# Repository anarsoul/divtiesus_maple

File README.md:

# [DivTIESUS Maple Edition](https://anarsoul.github.io/divtiesus_maple)
DivTIESUS Maple Edition is a SD/MMC card interface for the ZX Spectrum. It is based on Miguel's [DivTIESUS](https://github.com/mcleod-ideafix/divtiesus), but adds joystick port and serial port for WiFi at the expense of Soft +3E feature. I redid whole project in KiCAD and rerouted the PCB. CPLD pin assignment has been changed to accommodate new PCB layout.

You can [buy me a coffee](https://ko-fi.com/anarsoul) if you want to say thank you.

# Features
- DivMMC compatible interface with 8 KiB of EEPROM and 128 KiB or 512 KiB of RAM. Standard utils for EEPROM flashing, as provided by the ESXDOS team, are compatible with DivTIESUS.
- Model autodetection. This means you don't need to put a jumper, or flip a switch to change from using it with a Spectrum 48K and a +3.
- Tested with original Spectrum+, Black +2, Harlequin 128 rev. 2D and rev. 4B, Karabas 128 rev. B1. More testing reports will be appreciated
- It uses its own fast clock (24 MHz). It does not need the CPU clock at all.
- NMI button to call file browser in ESXDOS, and handy RESET button.
- MicroSD card slot
- DIP switches for enabling EEPROM flashing and disabling auto-mapping (bottom switch) and for disabling built-in joystick interface (top switch)
- Optional: Zx-Uno-compatible UART (running at 115200 baud) with WiFi. Do not place ESP12 if you are not planning to use it
- Optional: Built-in Kempston joystick interface, compatible with either Atari-style joystick or Sega Genesis joystick (3 or 6-button). Do not place DB9 connector and U6 (74HC165) if you are not planning to use it and disable it with a DIP switch. All 3 buttons are implemented (so called "extended Kempston")
- Joystick interface maps "A" button as "UP" if "Start" button is pressed during machine reset.
- Visual feedback for SD activity (blue led)
- ESXDOS shadowing does not collide with all-RAM feature in +2A/B/3 machines. If the system is in all-RAM mode, ESXDOS ROM mapping is disabled.
- Included STLs for 3D printing an enclosure

# Pictures

# Schematic

Schematics can be found [here](out/schematics.pdf)

# Build
- First, you need the DivTIESUS Maple Edition PCB. You can order it from JLCPCB or from PCBWay using `divtiesus_maple_rev2.zip` file from out directory. There is also a [project on PCBWay](https://www.pcbway.com/project/shareproject/DivTIESUS_Maple_Edition_rev_2_c9d0d700.html) if you want to support me
- Second, source the components. Most of the components are rather standard so you can buy it off DigiKey or Mouser. All of them can also be obtained from AliExpress. Be careful with components from Aliexpress, especially if the price is too good to be true

## Bill of materials

Interactive BOM can be found [here](out/bom/ibom.html)

Links to some components:

|Qty|Component|Link|
|--------|---------|--------|
|1|EPM240T100|[link](https://www.aliexpress.com/item/1005003990429762.html)|
|1|DIP switches, 2 position|[link](https://www.aliexpress.com/item/33027764033.html)|
|1|RAM|[link](https://www.aliexpress.com/item/1005002495799688.html)|
|1|EEPROM|[link](https://www.aliexpress.com/item/1005003773070206.html)|
|1|ZX Bus connector, 56pin|[link](https://www.aliexpress.com/item/1005002212044956.html)|
|2|Buttons, 6x6x6H|[link](https://www.aliexpress.com/item/1005005129319965.html)|
|1|microSD slot|[link](https://www.aliexpress.com/item/1005006255074403.html)|
|1|Crystal oscillator, 24Mhz|[link](https://www.aliexpress.com/item/1005005879624979.html)|

- The oscillator does not need to be 24 MHz, but if you use a different value, you'll have to resynthesize CPLD image, otherwise WiFi will not work
- I usually start with placing the CPLD first and programming it. Note: you'll need to supply 3.3V in order to program CPLD, there are GND and 3.3V test points left for this purpose. I source CPLDs from Aliexpress and some of them are coming dead. It is easier to test and replace it before the rest of the components are populated.
- Then place the passives (resistors, resistor arrays, capacitors) and the LED
- Then RAM, EEPROM, microSD socket, DB9 connector and ESP12. You can either leave EEPROM blank or preprogram it. Either way is fine, it can be programmed in-system later, but having EEPROM with known contents may simplify troubleshooting

## First electrical testing
- Check that there is no shorts on the 5V and 3.3V power rails.
- Use a microscope or a magnifying glass to check that there is no shorts between adjacent pads at the CPLD chip.

After all the checks, proceed to build and solder the ZX Spectrum bus connector:

## ZX Spectrum bus connector
- Take the 2x28 pin edge connector and cut about 1-2mm on each side to leave the ends opened, refer to original DivTIESUS README.
- Pull and extract the two metal contacts that are positioned at 5th place, where the index tab will be placed
- Now take a small piece you can get from a PCB, 1.5mm thick and 7mm tall. This will be the index tab.
- As an alternative, you can 3D-print the tab, you can find the model [here](https://www.thingiverse.com/thing:6556638)
- Place the tab in the index hole. Sand it if it's too tall for the hole.
- Using a pair of pliers, push it in place. If it's too small for the hole, use some glue to keep it from coming loose.

Now the edge connector is ready to work as a ZX Spectrum rear bus connector!

## Enclosure

Enclosure can be printed in pretty much any plastic. You need `button-2-nmi.stl`, `button-2-reset.stl`, `enclosure.stl` and `enclosure_top.stl` or `enclosure_top_no_jtag_no_switch.stl` if you don't want the holes for JTAG and the switch. Personally, I printed the parts in PLA and PETG. ABS should work as well. Keep in mind that PLA will soften at ~60C, so avoid using it for enclosure if you are planning to use the device with an original machine. Modern clones are fine, they are usually using CMOS ICs and modern voltage regulators that do not produce much heat.

First, place the buttons, short button (reset) closer to the edge

Then insert the PCB. Be careful to keep it straight and don't let the buttons to fall out

Use 4 M2x8 screws to fix enclosure top

## WiFi

DivTiesus Maple Edition implements Zx-Uno-compatible UART, so software compiled for Zx-Uno should work with it.

I recommend using Nihirash's software, [Netman](https://github.com/nihirash/netman-zx) and [Moon Rabbit](https://github.com/nihirash/moon-rabbit-zx). The binaries can be found [here](tools/wifi/zxwifi.zip) - just unpack them onto your SD card and run `netman/NETMAN.BAS` to configure WiFi. WiFi configuration is persistent, so it needs to be done once. Once WiFi is configured you can run `moon_rabbit/MOONR.BAS` to browse gopher sites.

You can also check out my tool for transferring files from PC to Spectrum: [zxmit](https://github.com/anarsoul/zxmit)

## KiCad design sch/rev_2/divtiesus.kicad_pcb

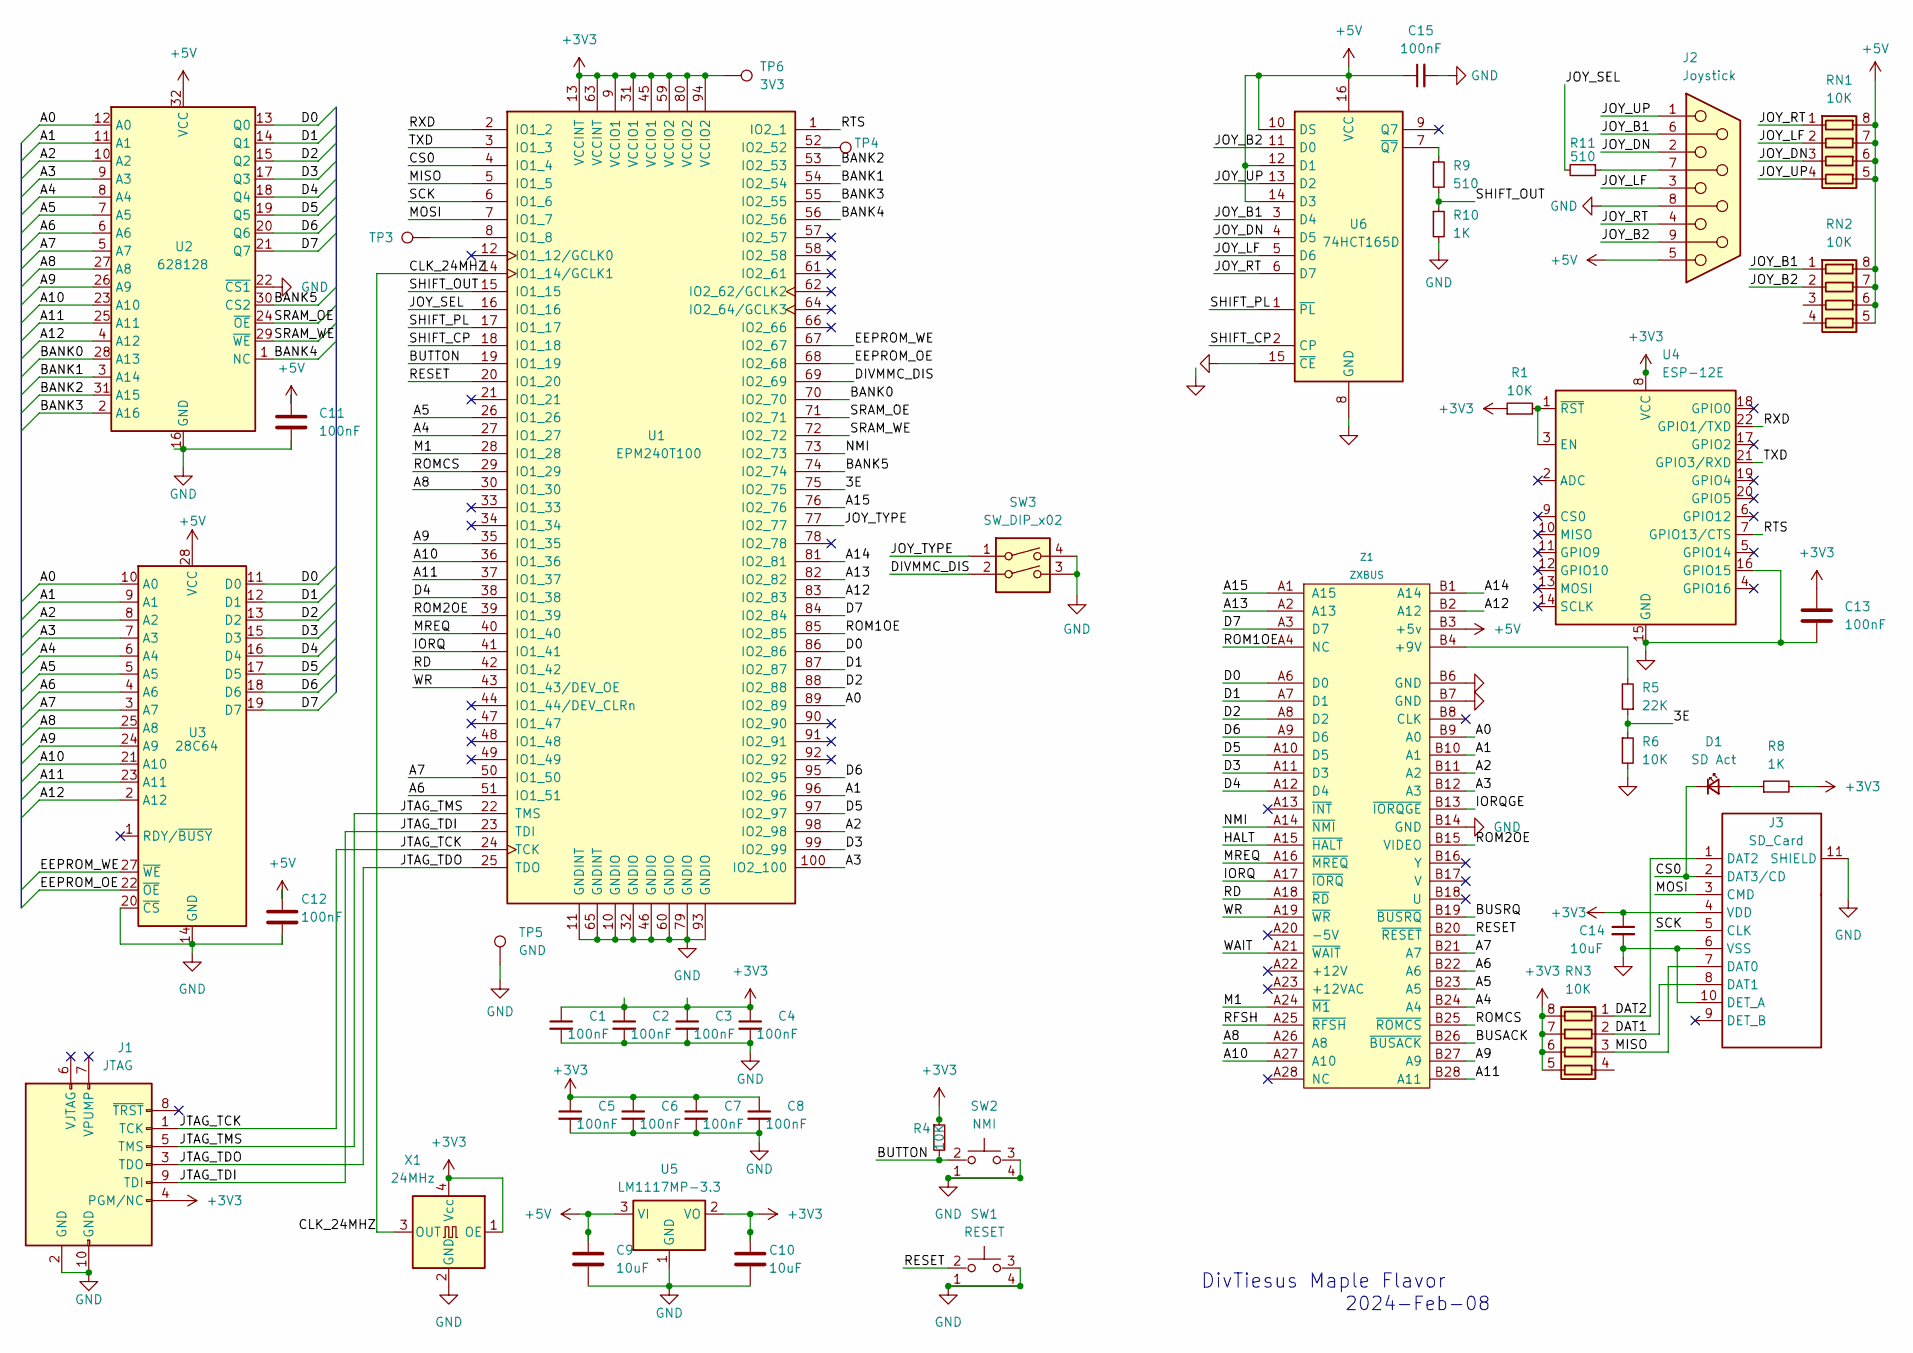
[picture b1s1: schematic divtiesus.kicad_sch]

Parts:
C1, C2, C3, C4, C5, C6, C7, C8, C11, C12, C13, C15: 100nF; C_0603_1608Metric
C9, C10, C14: 10uF; C_0805_2012Metric
D1: SD Act; LED_0805_2012Metric
J1: JTAG; IDC-Header_2x05_P2.54mm_Vertical
J2: Joystick; DSUB-9_Male_Vertical_P2.77x2.84mm
J3: SD_Card; microSD_HC_Hirose_DM3D-SF; PARTREV AX6
R1, R4, R6: 10K; R_0603_1608Metric
R5: 22K; R_0603_1608Metric
R8, R10: 1K; R_0603_1608Metric
R9, R11: 510; R_0603_1608Metric
RN1, RN2, RN3: 10K; R_Array_Convex_4x0603
SW1: RESET; SW_Tactile_SPST_Angled_PTS645Vx58-2LFS
SW2: NMI; SW_Tactile_SPST_Angled_PTS645Vx58-2LFS
SW3: SW_DIP_x02; SW_DIP_SPSTx02_Slide_Copal_CHS-02B_W7.62mm_P1.27mm
TP3, TP4: TestPoint_Pad_1.0x1.0mm
TP5: GND; TestPoint_Pad_1.0x1.0mm
TP6: 3V3; TestPoint_Pad_1.0x1.0mm
U1: EPM240T100; TQFP-100_14x14mm_P0.5mm
U2: 628128; SSOP-32_11.305x20.495mm_P1.27mm
U3: 28C64; SOIC-28W_7.5x17.9mm_P1.27mm
U4: ESP-12E
U5: LM1117MP-3.3; SOT-223-3_TabPin2
U6: 74HCT165D; SOIC-16_3.9x9.9mm_P1.27mm
X1: 24MHz; Oscillator_SMD_SeikoEpson_SG8002CE-4Pin_3.2x2.5mm
Z1: ZXBUS; CONECTOR_SIMPLE_CARA

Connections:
+3V3: C1.1, C2.1, C3.1, C4.1, C5.1, C6.1, C7.1, C8.1, C10.1, C13.1, C14.1, J1.4 (PGM/NC), J3.4 (VDD), R1.1, R4.1, R8.2, RN3.5 (R4.2), RN3.6 (R3.2), RN3.7 (R2.2), RN3.8 (R1.2), TP6.1, U1.9 (VCCIO1), U1.13 (VCCINT), U1.31 (VCCIO1), U1.45 (VCCIO1), U1.59 (VCCIO2), U1.63 (VCCINT), U1.80 (VCCIO2), U1.94 (VCCIO2), U4.8 (VCC), U5.2 (VO), X1.1 (OE), X1.4 (Vcc)
+5V: C9.1, C11.1, C12.1, C15.1, J2.5, RN1.5 (R4.2), RN1.6 (R3.2), RN1.7 (R2.2), RN1.8 (R1.2), RN2.5 (R4.2), RN2.6 (R3.2), RN2.7 (R2.2), RN2.8 (R1.2), U2.32 (VCC), U3.28 (VCC), U5.3 (VI), U6.10 (DS), U6.12 (D1), U6.14 (D3), U6.16 (VCC), Z1.B3 (+5v)
/3E: R5.1, R6.1, U1.75 (IO2_75)
/A0: U1.89 (IO2_89), U2.12 (A0), U3.10 (A0), Z1.B9 (A0)
/A1: U1.96 (IO2_96), U2.11 (A1), U3.9 (A1), Z1.B10 (A1)
/A2: U1.98 (IO2_98), U2.10 (A2), U3.8 (A2), Z1.B11 (A2)
/A3: U1.100 (IO2_100), U2.9 (A3), U3.7 (A3), Z1.B12 (A3)
/A4: U1.27 (IO1_27), U2.8 (A4), U3.6 (A4), Z1.B24 (A4)
/A5: U1.26 (IO1_26), U2.7 (A5), U3.5 (A5), Z1.B23 (A5)
/A6: U1.51 (IO1_51), U2.6 (A6), U3.4 (A6), Z1.B22 (A6)
/A7: U1.50 (IO1_50), U2.5 (A7), U3.3 (A7), Z1.B21 (A7)
/A8: U1.30 (IO1_30), U2.27 (A8), U3.25 (A8), Z1.A26 (A8)
/A9: U1.35 (IO1_35), U2.26 (A9), U3.24 (A9), Z1.B27 (A9)
/A10: U1.36 (IO1_36), U2.23 (A10), U3.21 (A10), Z1.A27 (A10)
/A11: U1.37 (IO1_37), U2.25 (A11), U3.23 (A11), Z1.B28 (A11)
/A12: U1.83 (IO2_83), U2.4 (A12), U3.2 (A12), Z1.B2 (A12)
/A13: U1.82 (IO2_82), Z1.A2 (A13)
/A14: U1.81 (IO2_81), Z1.B1 (A14)
/A15: U1.76 (IO2_76), Z1.A1 (A15)
/BANK0: U1.70 (IO2_70), U2.28 (A13)
/BANK1: U1.54 (IO2_54), U2.3 (A14)
/BANK2: U1.53 (IO2_53), U2.31 (A15)
/BANK3: U1.55 (IO2_55), U2.2 (A16)
/BANK4: U1.56 (IO2_56), U2.1 (NC)
/BANK5: U1.74 (IO2_74), U2.30 (CS2)
/BUSACK: Z1.B26 (~BUSACK)
/BUSRQ: Z1.B19 (~BUSRQ)
/BUTTON: R4.2, SW2.2, U1.19 (IO1_19)
/CLK_24MHZ: U1.14 (IO1_14/GCLK1), X1.3 (OUT)
/CS0: D1.1 (K), J3.2 (DAT3/CD), U1.4 (IO1_4)
/D0: U1.86 (IO2_86), U2.13 (Q0), U3.11 (D0), Z1.A6 (D0)
/D1: U1.87 (IO2_87), U2.14 (Q1), U3.12 (D1), Z1.A7 (D1)
/D2: U1.88 (IO2_88), U2.15 (Q2), U3.13 (D2), Z1.A8 (D2)
/D3: U1.99 (IO2_99), U2.17 (Q3), U3.15 (D3), Z1.A11 (D3)
/D4: U1.38 (IO1_38), U2.18 (Q4), U3.16 (D4), Z1.A12 (D4)
/D5: U1.97 (IO2_97), U2.19 (Q5), U3.17 (D5), Z1.A10 (D5)
/D6: U1.95 (IO2_95), U2.20 (Q6), U3.18 (D6), Z1.A9 (D6)
/D7: U1.84 (IO2_84), U2.21 (Q7), U3.19 (D7), Z1.A3 (D7)
/DAT1: J3.8 (DAT1), RN3.2 (R2.1)
/DAT2: J3.1 (DAT2), RN3.1 (R1.1)
/DIVMMC_DIS: SW3.2, U1.69 (IO2_69)
/EEPROM_OE: U1.68 (IO2_68), U3.22 (~OE)
/EEPROM_WE: U1.67 (IO2_67), U3.27 (~WE)
/HALT: Z1.A15 (~HALT)
/IORQ: U1.41 (IO1_41), Z1.A17 (~IORQ)
/IORQGE: Z1.B13 (~IORQGE)
/JOY_B1: J2.6, RN2.1 (R1.1), U6.3 (D4)
/JOY_B2: J2.9, RN2.2 (R2.1), U6.11 (D0)
/JOY_DN: J2.2, RN1.3 (R3.1), U6.4 (D5)
/JOY_LF: J2.3, RN1.2 (R2.1), U6.5 (D6)
/JOY_RT: J2.4, RN1.1 (R1.1), U6.6 (D7)
/JOY_SEL: R11.2, U1.16 (IO1_16)
/JOY_TYPE: SW3.1, U1.77 (IO2_77)
/JOY_UP: J2.1, RN1.4 (R4.1), U6.13 (D2)
/JTAG_TCK: J1.1 (TCK), U1.24 (TCK)
/JTAG_TDI: J1.9 (TDI), U1.23 (TDI)
/JTAG_TDO: J1.3 (TDO), U1.25 (TDO)
/JTAG_TMS: J1.5 (TMS), U1.22 (TMS)
/M1: U1.28 (IO1_28), Z1.A24 (~M1)
/MISO: J3.7 (DAT0), RN3.3 (R3.1), U1.5 (IO1_5)
/MOSI: J3.3 (CMD), U1.7 (IO1_7)
/MREQ: U1.40 (IO1_40), Z1.A16 (~MREQ)
/NMI: U1.73 (IO2_73), Z1.A14 (~NMI)
/RD: U1.42 (IO1_42), Z1.A18 (~RD)
/RESET: SW1.2, U1.20 (IO1_20), Z1.B20 (~RESET)
/RFSH: Z1.A25 (~RFSH)
/ROM1OE: U1.85 (IO2_85), Z1.A4 (NC)
/ROM2OE: U1.39 (IO1_39), Z1.B15 (VIDEO)
/ROMCS: U1.29 (IO1_29), Z1.B25 (~ROMCS)
/RTS: U1.1 (IO2_1), U4.7 (GPIO13/CTS)
/RXD: U1.2 (IO1_2), U4.22 (GPIO1/TXD)
/SCK: J3.5 (CLK), U1.6 (IO1_6)
/SHIFT_CP: U1.18 (IO1_18), U6.2 (CP)
/SHIFT_OUT: R9.2, R10.1, U1.15 (IO1_15)
/SHIFT_PL: U1.17 (IO1_17), U6.1 (~PL)
/SRAM_OE: U1.71 (IO2_71), U2.24 (~OE)
/SRAM_WE: U1.72 (IO2_72), U2.29 (~WE)
/TXD: U1.3 (IO1_3), U4.21 (GPIO3/RXD)
/WAIT: Z1.A21 (~WAIT)
/WR: U1.43 (IO1_43/DEV_OE), Z1.A19 (~WR)
GND: C1.2, C2.2, C3.2, C4.2, C5.2, C6.2, C7.2, C8.2, C9.2, C10.2, C11.2, C12.2, C13.2, C14.2, C15.2, J1.2 (GND), J1.10 (GND), J2.8, J3.6 (VSS), J3.10 (DET_A), J3.11 (SHIELD), R6.2, R10.2, SW1.1, SW1.3, SW1.4, SW2.1, SW2.3, SW2.4, SW3.3, SW3.4, TP5.1, U1.10 (GNDIO), U1.11 (GNDINT), U1.32 (GNDIO), U1.46 (GNDIO), U1.60 (GNDIO), U1.65 (GNDINT), U1.79 (GNDIO), U1.93 (GNDIO), U2.16 (GND), U2.22 (~CS1), U3.14 (GND), U3.20 (~CS), U4.15 (GND), U4.16 (GPIO15), U5.1 (GND), U6.8 (GND), U6.15 (~CE), X1.2 (GND), Z1.B6 (GND), Z1.B7 (GND), Z1.B14 (GND)
unnamed: D1.2 (A), R8.1
unnamed: J2.7, R11.1
unnamed: TP3.1, U1.8 (IO1_8)
unnamed: TP4.1, U1.52 (IO2_52)
unnamed: R1.2, U4.1 (~RST), U4.3 (EN)
unnamed: R9.1, U6.7 (~Q7)
unnamed: R5.2, Z1.B4 (+9V)

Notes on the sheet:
2024-Feb-08
DivTiesus Maple Flavor

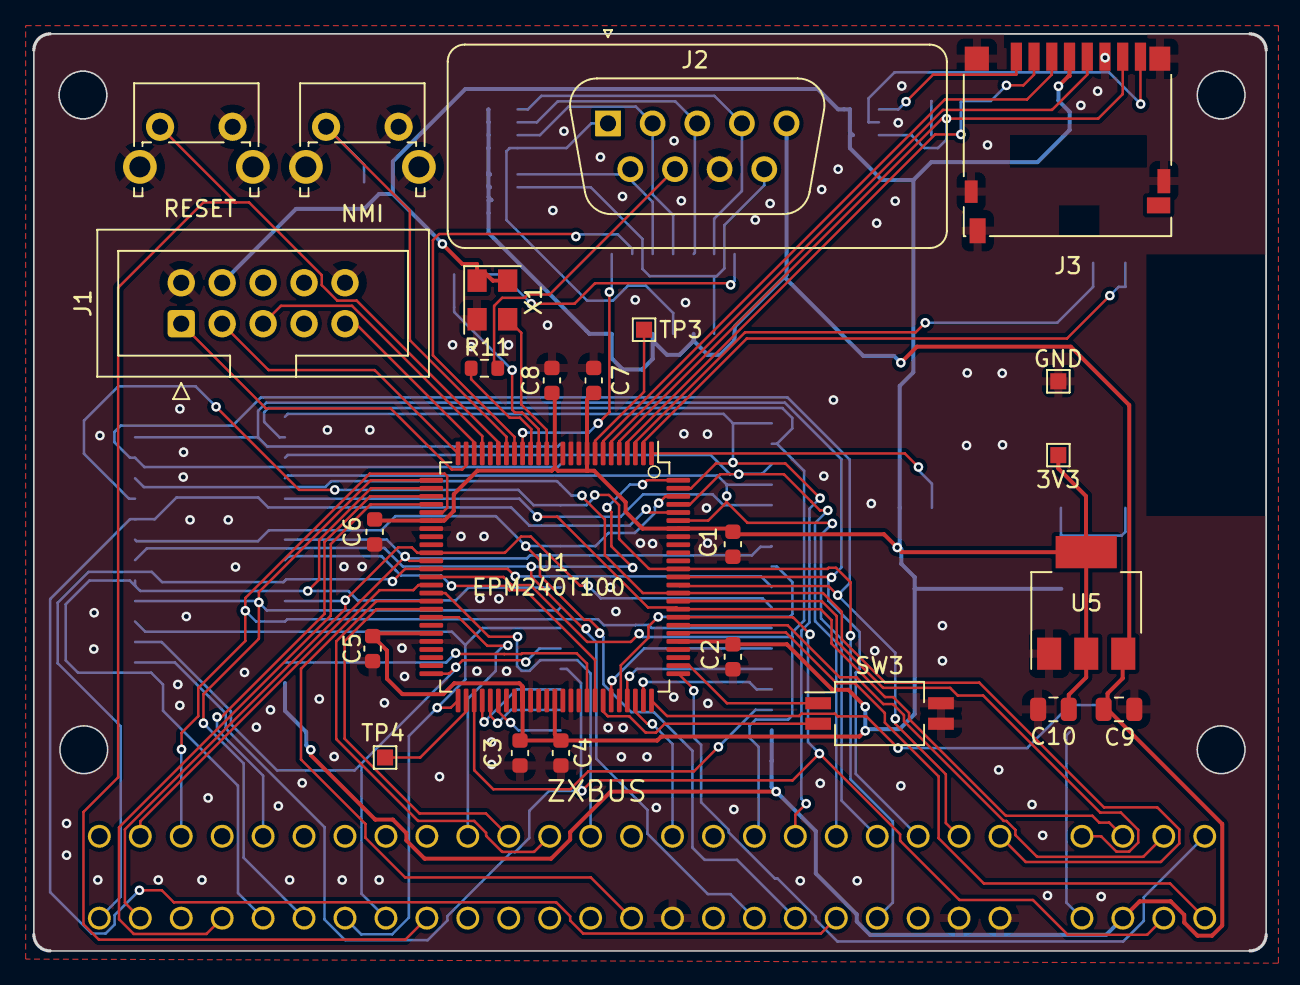
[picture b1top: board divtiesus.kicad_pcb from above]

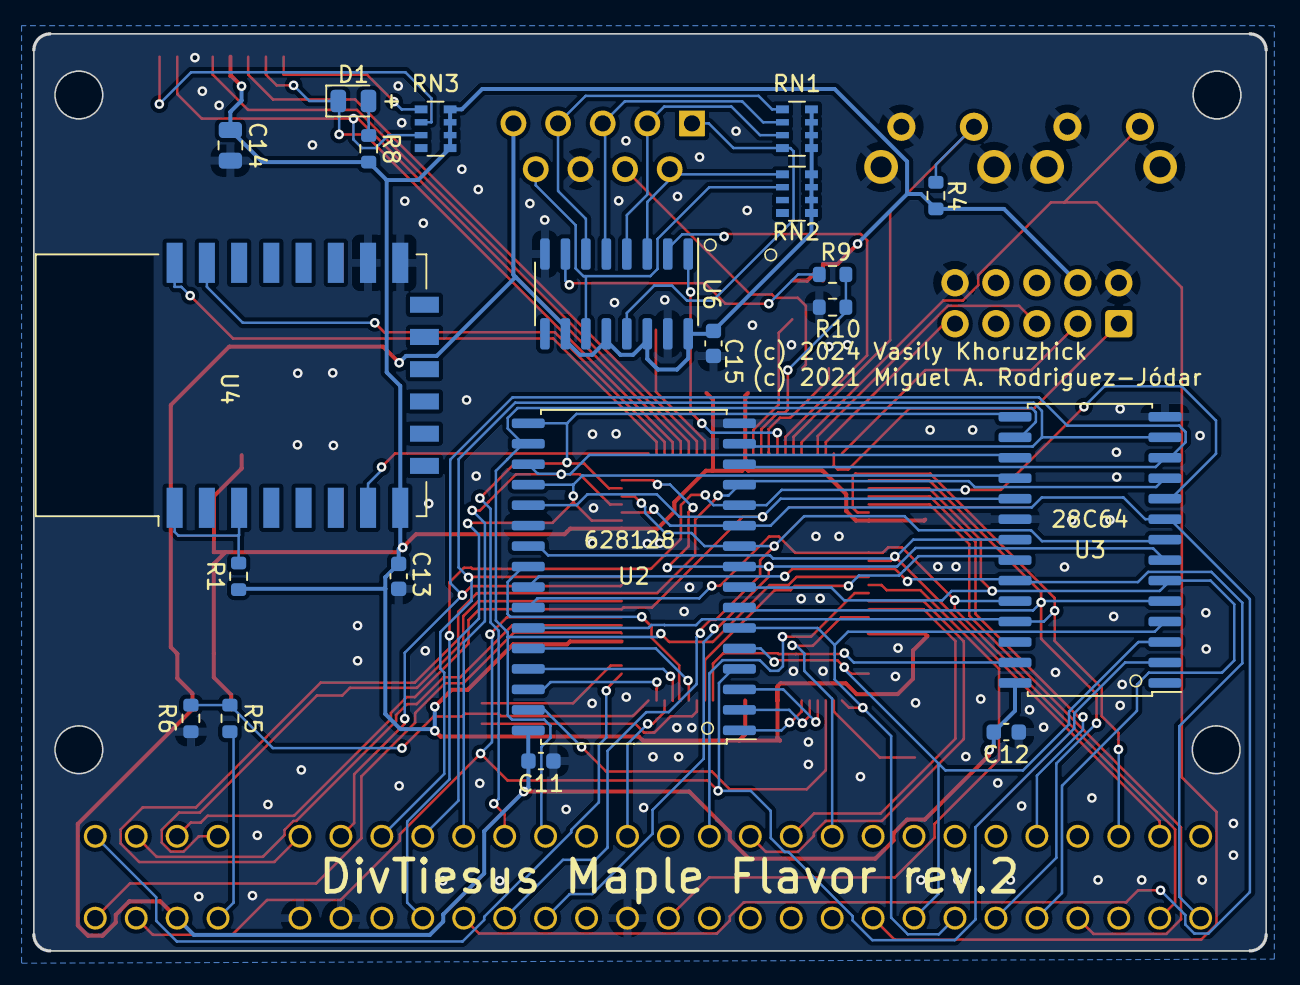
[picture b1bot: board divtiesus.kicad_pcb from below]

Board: 2 copper layers, 76.5 x 56.9 mm, 45 parts (20 on the bottom side), 82 nets.

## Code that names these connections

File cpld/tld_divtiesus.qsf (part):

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set_location_assignment PIN_3 -to uart_tx
set_location_assignment PIN_1 -to uart_rts
set_location_assignment PIN_15 -to shift_q
set_location_assignment PIN_18 -to shift_cp
set_location_assignment PIN_17 -to shift_pl
set_location_assignment PIN_16 -to joy_sel
set_global_assignment -name POWER_PRESET_COOLING_SOLUTION "NO HEAT SINK WITH STILL AIR"
set_instance_assignment -name CURRENT_STRENGTH_NEW 8MA -to d[7]
set_instance_assignment -name CURRENT_STRENGTH_NEW 8MA -to d[6]
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set_global_assignment -name DEVICE_FILTER_SPEED_GRADE 5
set_global_assignment -name OPTIMIZATION_MODE BALANCED
set_instance_assignment -name WEAK_PULL_UP_RESISTOR ON -to nmi_button_n
set_location_assignment PIN_29 -to romcs
set_instance_assignment -name CURRENT_STRENGTH_NEW "MAXIMUM CURRENT" -to romcs
set_instance_assignment -name IO_STANDARD "3.3-V LVTTL" -to romcs
set_instance_assignment -name IO_STANDARD "3.3-V LVTTL" -to romoe2
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
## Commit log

2024-05-07 Initial commit for CPLD code
2024-10-19 Bad SD workaround
2024-10-19 Add schematics, IBOM, case STLs, kicad project
2024-12-18 Recompile pof file and move it to out directory
2024-12-19 Add top enclosure without JTAG and switch holes
2024-12-23 cpld: implement jumper to disable joystick interface
2024-12-23 Cosmetic fix: change R1 footprint from C_0603 to R_0603 and update IBOM
2024-12-23 README: fix links to PDF and IBOM
2024-12-23 README: add a link to PCBWay project
2024-12-23 README: add link to github pages
2024-12-23 README: mention necessary files for enclosure
    Also rename out/case to out/enclosure
2024-12-23 README: add Aliexpress link to EPM240
2024-12-24 Update README with testing reports
2024-12-25 Add terminal app for ESP debugging
2025-03-20 README.md: add my ko-fi link
2025-09-24 Revert "Switch UART to Spectrum Next-like interface"
    This reverts commit e17d2df9fd5a1b8940326b4a016df15eee8210e9.
2025-09-24 Add instructions for WiFi and pre-compiled binaries
2025-09-24 Switch UART to Spectrum Next-like interface

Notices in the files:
cpld/tld_divtiesus.qsf:
Copyright (C) 2020  Intel Corporation. All rights reserved.
sch/rev_2/divtiesus.kicad_pcb:
(c) 2024 Vasily Khoruzhick
(c) 2021 Miguel A. Rodriguez-Jódar
